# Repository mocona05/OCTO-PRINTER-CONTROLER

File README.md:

# OCTO-PRINTER TFT-LCD HAT MOUDLE (3D PRINTER)

**1. DC 7~30V INPUT(DC12V or DC24V, 5V 4A OUT)**

**2. POWER SUPPLY UNIT CONTROL( EXTERNAL RELAY CONTROL 12V or 24V Relay)**

**3. RGBW LED STRIP CONTROL(RED, BLUE, GREEN, WHITE LED FET SWITCHING CONTROL)**

https://ko.aliexpress.com/item/33022691125.html?spm=a2g0o.productlist.0.0.248165f1OyU0S3&algo_pvid=781429ec-3f9b-4be9-987b-c59219aeeffd&algo_expid=781429ec-3f9b-4be9-987b-c59219aeeffd-22&btsid=0bb0624416065510941383430e2371&ws_ab_test=searchweb0_0,searchweb201602_,searchweb201603_

**4. Raspberry SPI INTERFACE TFT-LCD & TOUCH SUPPORT**

https://ko.aliexpress.com/item/32233522592.html?spm=a2g0s.9042311.0.0.5f7c4c4dNYOjiv

**5. ENCLOSURE-CONTROL SUPPORT (HUMIDITY, TEMPERATURE MONITORING, OUTPUT RELAY 4CHANNEL CONTROL SUPPORT)**

**6. Raspberry Pi AP Cooling FAN(5V, PWM Speed Control)**

**7. Klipper ADXL345 Sensor Connector Bulit in(ADXL345 resonance sensor cannot be used simultaneously with SPI-LCD.)**

https://www.klipper3d.org/Measuring_Resonances.html

For more information, see WIKI.<br>
https://github.com/mocona05/OCTO-PRINTER-CONTROLER/wiki

Application of Octo Printer Shiled<br>
https://www.thingiverse.com/make:639404

LCD module Pi TFT 3.5 inch (320*480) Touchscreen Display Module

**TOUCH GHI SETTING**

OCTO PRINTER IMAGE DOWN LOAD
https://octoprint.org/download/

OCTO PRINTER IMAGE to SD MEMORY WRITE

https://www.raspberrypi.org/forums/viewtopic.php?t=131489
https://www.raspberrypi.org/forums/viewtopic.php?p=890408#p890408

**RASPBERRY PI FIRMWARE UPDATE**

`sudo rpi-update`

**RASPBERRY PI UPDATE**

`sudo apt-get update`<br>
`sudo apt-get upgrade`<br>

**RASPBERRY PI XWINDOWS INSTALL**

`sudo apt-get install --no-install-recommends xserver-xorg`<br>
`sudo apt-get install --no-install-recommends xinit`<br>
`sudo apt-get install raspberrypi-ui-mods`<br>

**xwindos auto login & Pi camera setting**

`sudo raspi-config`<br>
3.Boot-option -> B1 Desktop /CLI -> B4 Desktop Autologin

Pi CAMERA SETUP (Raspberry pi camera used)
5. Interfacing Optin -> Pi Camera -> Yes

7.Advanced Options -> A1 Expand Filesystem

**TFT DRIVER INSTALL**

https://www.waveshare.com/wiki/3.5inch_RPi_LCD_(A)#Method_1._Driver_installation

`wget https://www.waveshare.com/w/upload/1/1e/LCD-show-180817.tar.gz`<br>

**DRIVER extractor**

`tar xvf LCD-show-180817.tar.gz`<br>
`cd LCD-show/`<br>
`chmod 777 LCD35-show`<br>
`./LCD35-show`<br>

**HDMI & TOUCH DRIVER INSTALL**

https://www.raspberrypi.org/forums/viewtopic.php?t=175616

`sudo apt-get install xinput-calibrator`<br>

**CHROMIUM INSTALL**

`sudo apt-get install unclutter`<br>
`sudo apt-get install xdotool`<br>

https://raspberrypi.stackexchange.com/questions/374/how-do-i-install-google-chrome

`sudo apt-get install chromium-browser`<br>

**CHROMIUM AUTO START SETTING**

https://www.raspberrypi.org/forums/viewtopic.php?t=163316

`sudo nano ~/.config/lxsession/LXDE-pi/autostart`<br>
`sudo -u pi chromium-browser --kiosk --incognito http://127.0.0.1 &`<br>

`sudo reboot`

connect at http://<your Raspberry pi's IP>

**PSU Control Plug In Setup**

**LED Strip Control Plug in Setup**

**TouchUI Plug in Setup**

**USB CAM Install(Option)**

https://github.com/jacksonliam/mjpg-streamer/

`sudo apt-get install subversion libjpeg8-dev libav-tools libv4l-dev cmake`<br>
`git clone https://github.com/jacksonliam/mjpg-streamer.git`<br>
`cd mjpg-streamer/mjpg-streamer-experimental`<br>
`export LD_LIBRARY_PATH=.`<br>
`sudo make`<br>

Connecting camera repeat command.

`ls /dev/video*`<br> 
(If you see the / dev / video0, then everything should be fine, go ahead)

ttps://github.com/foosel/OctoPrint/wiki/MJPG-Streamer-configuration

`sudo ./mjpg_streamer –i "./input_uvc.so –f 2 -y" -o "./output_http.so"`

check at http://<your Raspberry pi's IP>:8080/?action=stream

`sudo usermod -a -G video pi`<br>
(to allow user access to a device video, it is necessary to add it to the appropriate group)

`sudo make install`<br>
`cd ~`<br>
`sudo nano webcam-streamer`<br>

`#!/bin/bash`<br>
`Daemon=mjpg_streamer`<br>
`DaemonBase=/usr/local`<br>
`DaemonArgs="-i \"input_uvc.so –f 2 -y\" -o \"output_http.so\""`<br>
`case "" in`<br>
`start)`<br>
`eval LD_LIBRARY_PATH=${DaemonBase}/lib ${DaemonBase}/bin/${Daemon} ${DaemonArgs} >/dev/null 2>&1 &`<br>
`echo ": started"`<br>
`;;`<br>
`stop)`<br>
`pkill -x ${Daemon}`<br>
`echo ": stopped"`<br>
`;;`<br>
`*)`<br>
`echo "Usage:  {start|stop}" >&2`<br>
`;;`<br>
`Esac`<br>

`sudo chmod +x webcam-streamer`<br>
`sudo mv webcam-streamer /usr/local/bin/`<br>
`sudo nano ~/.octoprint/config.yaml`<br>

`system:`<br>
  `actions:`<br>
  `- action: streamon`<br>
    `command: sudo /usr/local/bin/webcam-streamer start`<br>
    `confirm: false`<br>
    `name: Start video stream`<br>
  `- action: streamoff`<br>
    `command: sudo /usr/local/bin/webcam-streamer stop`<br>
    `confirm: false`<br>
    `name: Stop video stream`<br>

**Auto start cam**

`sudo nano /etc/rc.local`<br>

`usr/local/bin/webcam-streamer start`<br>
(Just make sure to put it above the line that reads exit 0).

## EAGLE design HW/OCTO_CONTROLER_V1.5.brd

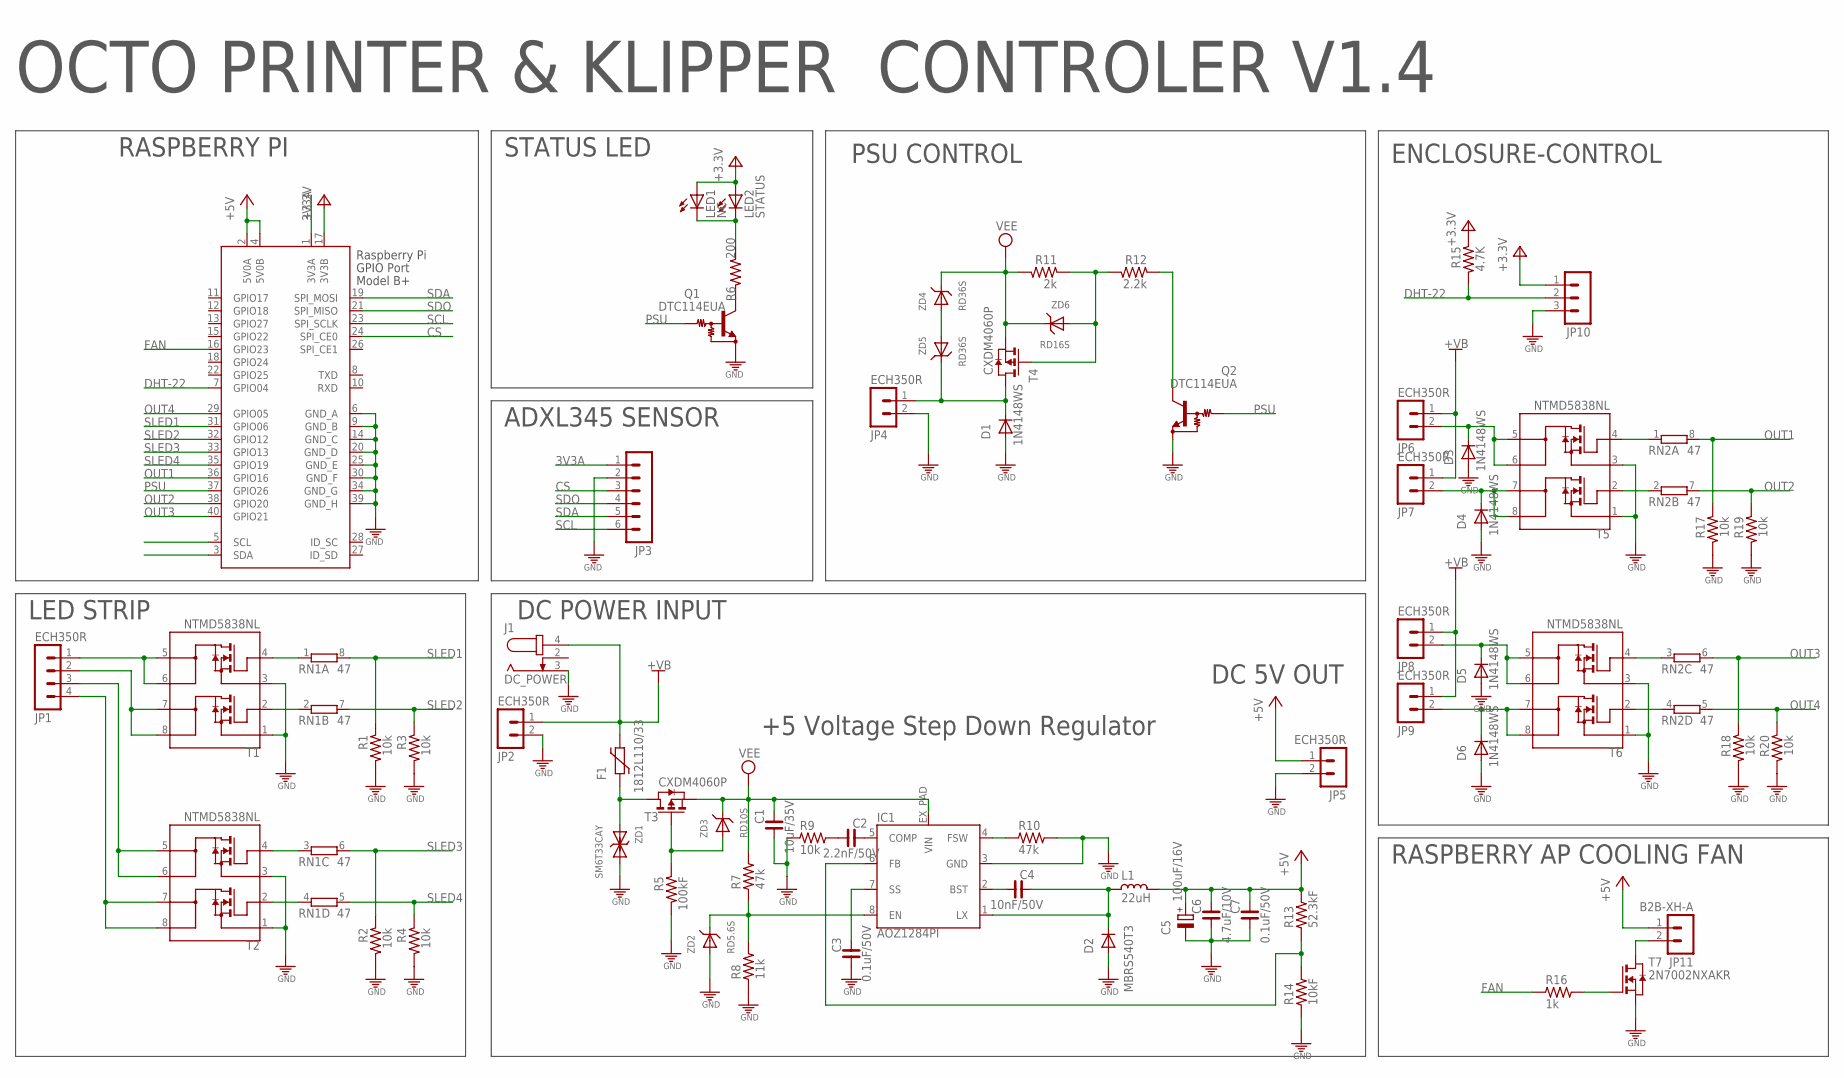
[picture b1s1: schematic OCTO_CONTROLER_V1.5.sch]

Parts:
C1: 10uF/35V; C3225
C2: 2.2nF/50V; C0603
C3, C7: 0.1uF/50V; C0603
C4: 10nF/50V; C0603
C5: 100uF/16V; D/7343-31W
C6: 4.7uF/10V; C2012
D1, D3, D4, D5, D6: 1N4148WS; SOD323
D2: MBRS540T3; SMC
F1: 1812L110/33; 1812L
IC1: AOZ1284PI; S08-EP1
J1: DC_POWER; DC-005
JP1: ECH350R; ECH350R-04
JP2, JP4, JP6, JP7, JP8, JP9: ECH350R; ECH350R-02
JP3: MA06-1SMALL; MA06-1-S
JP5: ECH350R; ECH350V-02
JP10: MA03-1ECH350R; ECH350R-03
JP11: B2B-XH-A; MOLEX5267-02
L1: 22uH; SHP1260P-F
LED1: NC; LED-1608
LED2: STATUS; 3FG2HD-T1
Q1, Q2: DTC114EUA; SC59-BEC
R1, R2, R3, R4, R9, R17, R18, R19, R20: 10k; R0603
R5: 100kF; R0603
R6: 200; R0603
R7, R10: 47k; R0603
R8: 11k; R0603
R11: 2k; R0603
R12: 2.2k; R0603
R13: 52.3kF; R0603
R14: 10kF; R0603
R15: 4.7K; R0603
R16: 1k; R0603
RN1, RN2: 47; ARRAY_R3216
T1, T2, T5, T6: NTMD5838NL; SO08
T3, T4: CXDM4060P; SOT89
T7: 2N7002NXAKR; SOT23
X1: RASPI_BOARD_B+#_F; RASPI_BOARD_B+_FULL
ZD1: SM6T33CAY; SMB
ZD2: RD5.6S; DSMM
ZD3: RD10S; DSMM
ZD4, ZD5: RD36S; DSMM
ZD6: RD16S; DSMM

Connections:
3V3: JP10.1, LED1.A, LED2.A, R15.1, X1.17 (3V3B)
3V3A: JP3.1, X1.1 (3V3A)
+5V: C5.+, C6.1, C7.1, JP5.1, JP11.1, L1.1, R13.2, X1.2 (5V0A), X1.4 (5V0B)
+12V: F1.P$2 (2), J1.4 (3), JP2.1, JP6.1, JP7.1, JP8.1, JP9.1
CS: JP3.3, X1.24 (SPI_CE0)
DC-IN: F1.P$1 (1), T3.2 (D), T3.2@1 (D), ZD1.A
DHT-22: JP10.2, R15.2, X1.7 (GPIO04)
FAN: R16.1, X1.16 (GPIO23)
GND: C1.2, C3.2, C5.-, C6.2, C7.2, D1.A, D2.A, D3.A, D4.A, D5.A, D6.A, IC1.3 (GND), J1.3 (1), JP2.2, JP3.2, JP4.2, JP5.2, JP10.3, Q1.1 (GND), Q2.1 (GND), R1.2, R2.2, R3.2, R4.2, R5.2, R8.1, R9.1, R10.2, R14.1, R17.2, R18.2, R19.2, R20.2, T1.1, T1.3, T2.1, T2.3, T5.1, T5.3, T6.1, T6.3, T7.S, X1.6 (GND_A), X1.9 (GND_B), X1.14 (GND_C), X1.20 (GND_D), X1.25 (GND_E), X1.30 (GND_F), X1.34 (GND_G), X1.39 (GND_H), ZD1.C (K), ZD2.A
unnamed: R11.1, R12.2, T4.3 (G), ZD6.A
unnamed: LED1.C, LED2.K (C), R6.1
unnamed: ZD4.A, ZD5.A
unnamed: RN1.2 (1), T1.2
unnamed: RN1.1, T1.4
unnamed: RN1.4 (1), T2.2
unnamed: JP11.2, T7.D
unnamed: R16.2, T7.G
unnamed: IC1.6 (FB), R13.1, R14.2
unnamed: RN1.3 (1), T2.4
unnamed: C4.2, IC1.2 (BST)
unnamed: D1.C, JP4.1, T4.2 (D), T4.2@1 (D), ZD5.C
unnamed: RN2.2 (1), T5.2
unnamed: RN2.1, T5.4
unnamed: D3.C, JP6.2, T5.5, T5.6
unnamed: D4.C, JP7.2, T5.7, T5.8
unnamed: RN2.4 (1), T6.2
unnamed: RN2.3 (1), T6.4
unnamed: C4.1, D2.C, IC1.1 (LX), L1.2
unnamed: IC1.4 (FSW), R10.1
unnamed: C3.1, IC1.7 (SS)
unnamed: IC1.8 (EN), R7.1, R8.2, ZD2.C
unnamed: C2.1, IC1.5 (COMP)
unnamed: Q2.3 (OUT), R12.1
unnamed: D5.C, JP8.2, T6.5, T6.6
unnamed: C2.2, R9.2
unnamed: D6.C, JP9.2, T6.7, T6.8
unnamed: Q1.3 (OUT), R6.2
unnamed: R5.1, T3.3 (G), ZD3.A
OUT1: R17.1, RN2.8 (2), X1.36 (GPIO16)
OUT2: R19.1, RN2.7 (2), X1.38 (GPIO20)
OUT3: R18.1, RN2.6 (2), X1.40 (GPIO21)
OUT4: R20.1, RN2.5 (2), X1.29 (GPIO05)
PSU: Q1.2 (IN), Q2.2 (IN), X1.37 (GPIO26)
S-LED1: JP1.1, T1.5, T1.6
S-LED2: JP1.2, T1.7, T1.8
S-LED3: JP1.3, T2.5, T2.6
S-LED4: JP1.4, T2.7, T2.8
SCL: JP3.6, X1.23 (SPI_SCLK)
SDA: JP3.5, X1.19 (SPI_MOSI)
SDO: JP3.4, X1.21 (SPI_MISO)
SLED1: R1.1, RN1.8 (2), X1.31 (GPIO06)
SLED2: R3.1, RN1.7 (2), X1.32 (GPIO12)
SLED3: R2.1, RN1.6 (2), X1.33 (GPIO13)
SLED4: R4.1, RN1.5 (2), X1.35 (GPIO19)
VEE: C1.1, IC1.EX_PAD (VIN), R7.2, R11.2, T3.1 (S), T4.1 (S), ZD3.C, ZD4.C, ZD6.C

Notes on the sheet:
OCTO PRINTER & KLIPPER CONTROLER V1.4
RASPBERRY PI
+5 Voltage Step Down Regulator
DC POWER INPUT
PSU CONTROL
STATUS LED
LED STRIP
DC 5V OUT
ENCLOSURE-CONTROL
ADXL345 SENSOR
RASPBERRY AP COOLING FAN

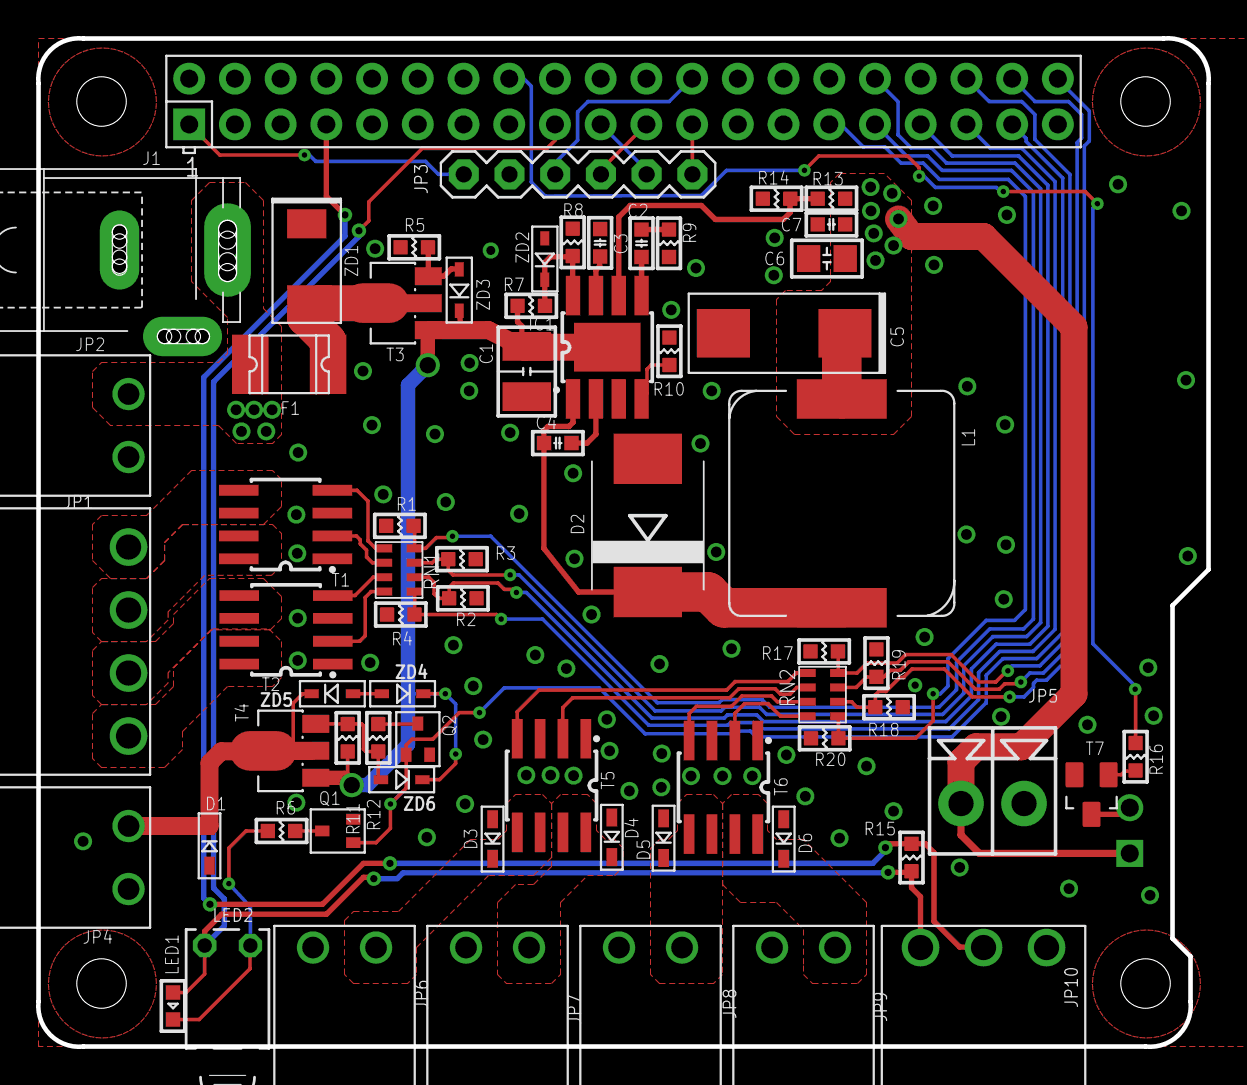
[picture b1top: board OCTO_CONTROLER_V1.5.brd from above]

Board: 2 copper layers, 65.0 x 56.0 mm, 68 parts (1 on the bottom side), 55 nets.

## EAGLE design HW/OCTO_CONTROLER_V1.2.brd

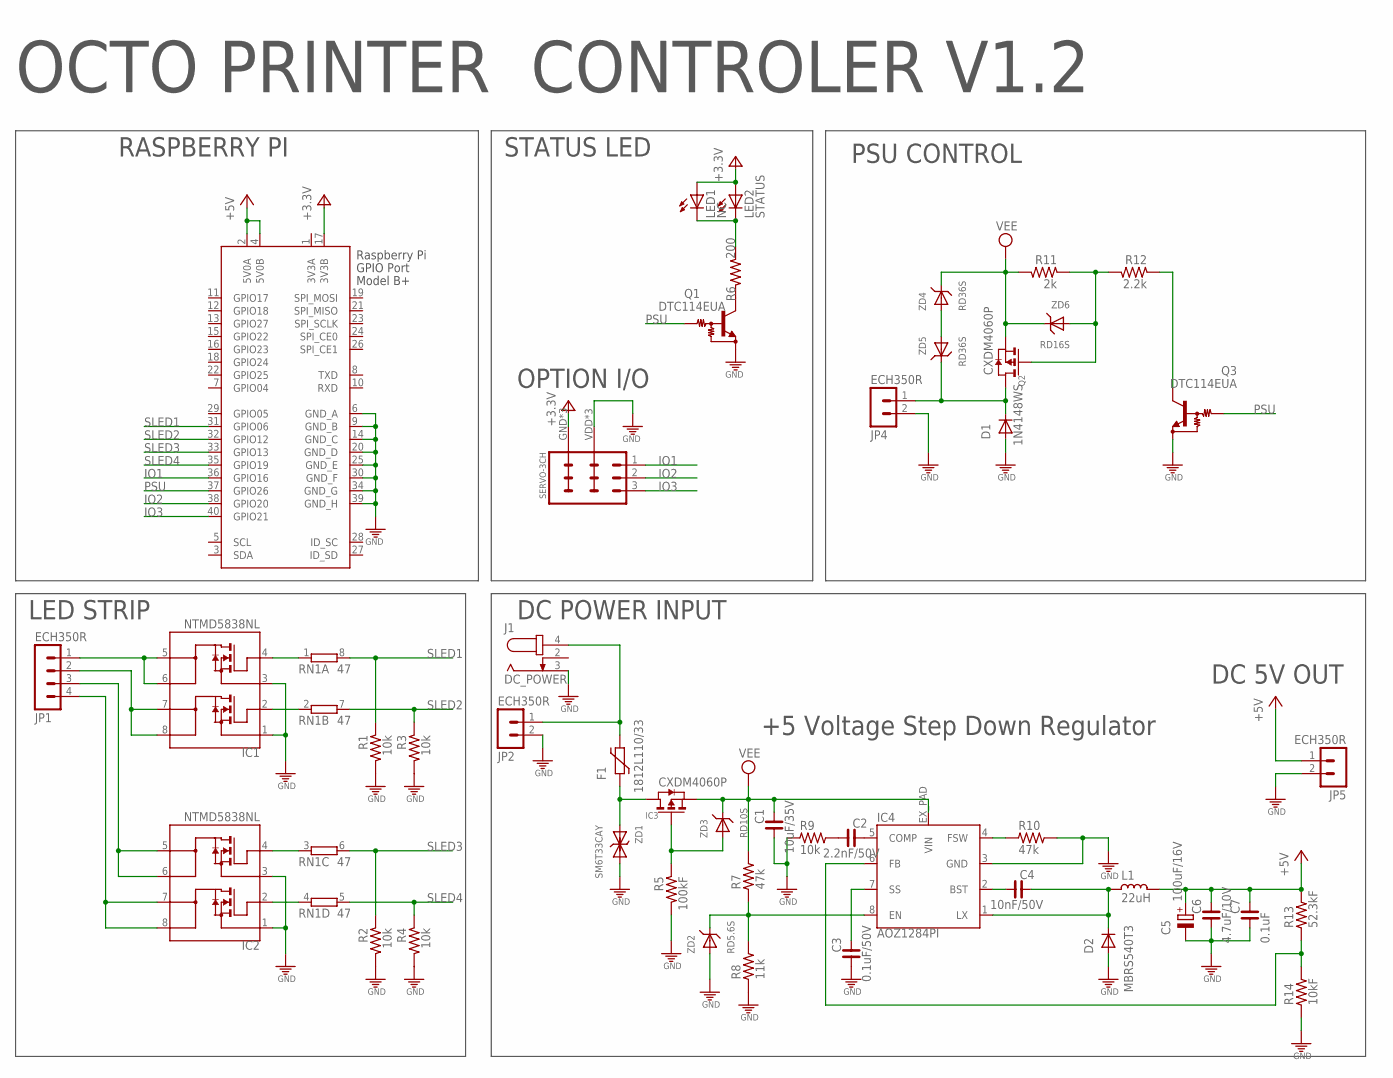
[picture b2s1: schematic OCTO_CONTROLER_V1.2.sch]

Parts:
C1: 10uF/35V; C3225
C2: 2.2nF/50V; C0603
C3: 0.1uF/50V; C0603
C4: 10nF/50V; C0603
C5: 100uF/16V; D/7343-31W
C6: 4.7uF/10V; C2012
C7: 0.1uF; C0603
D1: 1N4148WS; SOD323
D2: MBRS540T3; SMC
F1: 1812L110/33; 1812L
IC1, IC2: NTMD5838NL; SO08
IC3: CXDM4060P; SOT89
IC4: AOZ1284PI; S08-EP1
J1: DC_POWER; DC-005
JP1: ECH350R; ECH350R-04
JP2, JP4, JP5: ECH350R; ECH350R-02
JP3: SERVO-3CH; SERVO-3CH1
L1: 22uH; SHP1260P-F
LED1: NC; LED-1608
LED2: STATUS; 3FG2HD-T1
Q1, Q3: DTC114EUA; SC59-BEC
Q2: CXDM4060P; SOT89
R1, R2, R3, R4, R9: 10k; R0603
R5: 100kF; R0603
R6: 200; R0603
R7, R10: 47k; R0603
R8: 11k; R0603
R11: 2k; R0603
R12: 2.2k; R0603
R13: 52.3kF; R0603
R14: 10kF; R0603
RN1: 47; ARRAY_R3216
X1: RASPI_BOARD_B+#_F; RASPI_BOARD_B+_FULL
ZD1: SM6T33CAY; SMB
ZD2: RD5.6S; DSMM
ZD3: RD10S; DSMM
ZD4, ZD5: RD36S; DSMM
ZD6: RD16S; DSMM

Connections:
3V3: JP3.GND, JP3.GND@1 (GND), JP3.GND@2 (GND), LED1.A, LED2.A, X1.17 (3V3B)
3V3A: X1.1 (3V3A)
+5V: C5.+, C6.1, C7.1, JP5.1, L1.1, R13.2, X1.2 (5V0A), X1.4 (5V0B)
DC-IN: F1.P$1 (1), IC3.2 (D), IC3.2@1 (D), ZD1.A
GND: C1.2, C3.2, C5.-, C6.2, C7.2, D1.A, D2.A, IC1.1, IC1.3, IC2.1, IC2.3, IC4.3 (GND), J1.3 (1), JP2.2, JP3.VDD (+5V), JP3.VDD@1 (+5V), JP3.VDD@2 (+5V), JP4.2, JP5.2, Q1.1 (GND), Q3.1 (GND), R1.2, R2.2, R3.2, R4.2, R5.2, R8.1, R9.1, R10.2, R14.1, X1.6 (GND_A), X1.9 (GND_B), X1.14 (GND_C), X1.20 (GND_D), X1.25 (GND_E), X1.30 (GND_F), X1.34 (GND_G), X1.39 (GND_H), ZD1.C (K), ZD2.A
IO1: JP3.1, X1.36 (GPIO16)
IO2: JP3.2, X1.38 (GPIO20)
IO3: JP3.3, X1.40 (GPIO21)
unnamed: Q2.3 (G), R11.1, R12.2, ZD6.A
unnamed: LED1.C, LED2.K (C), R6.1
unnamed: ZD4.A, ZD5.A
unnamed: IC1.2, RN1.2 (1)
unnamed: IC1.4, RN1.1
unnamed: IC2.2, RN1.4 (1)
unnamed: IC4.6 (FB), R13.1, R14.2
unnamed: IC2.4, RN1.3 (1)
unnamed: C4.2, IC4.2 (BST)
unnamed: D1.C, JP4.1, Q2.2 (D), Q2.2@1 (D), ZD5.C
unnamed: C4.1, D2.C, IC4.1 (LX), L1.2
unnamed: IC4.4 (FSW), R10.1
unnamed: C3.1, IC4.7 (SS)
unnamed: IC4.8 (EN), R7.1, R8.2, ZD2.C
unnamed: C2.1, IC4.5 (COMP)
unnamed: Q3.3 (OUT), R12.1
unnamed: C2.2, R9.2
unnamed: Q1.3 (OUT), R6.2
unnamed: IC3.3 (G), R5.1, ZD3.A
unnamed: F1.P$2 (2), J1.4 (3), JP2.1
PSU: Q1.2 (IN), Q3.2 (IN), X1.37 (GPIO26)
S-LED1: IC1.5, IC1.6, JP1.1
S-LED2: IC1.7, IC1.8, JP1.2
S-LED3: IC2.5, IC2.6, JP1.3
S-LED4: IC2.7, IC2.8, JP1.4
SLED1: R1.1, RN1.8 (2), X1.31 (GPIO06)
SLED2: R3.1, RN1.7 (2), X1.32 (GPIO12)
SLED3: R2.1, RN1.6 (2), X1.33 (GPIO13)
SLED4: R4.1, RN1.5 (2), X1.35 (GPIO19)
VEE: C1.1, IC3.1 (S), IC4.EX_PAD (VIN), Q2.1 (S), R7.2, R11.2, ZD3.C, ZD4.C, ZD6.C

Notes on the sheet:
OCTO PRINTER CONTROLER V1.2
RASPBERRY PI
+5 Voltage Step Down Regulator
DC POWER INPUT
PSU CONTROL
STATUS LED
OPTION I/O
LED STRIP
DC 5V OUT

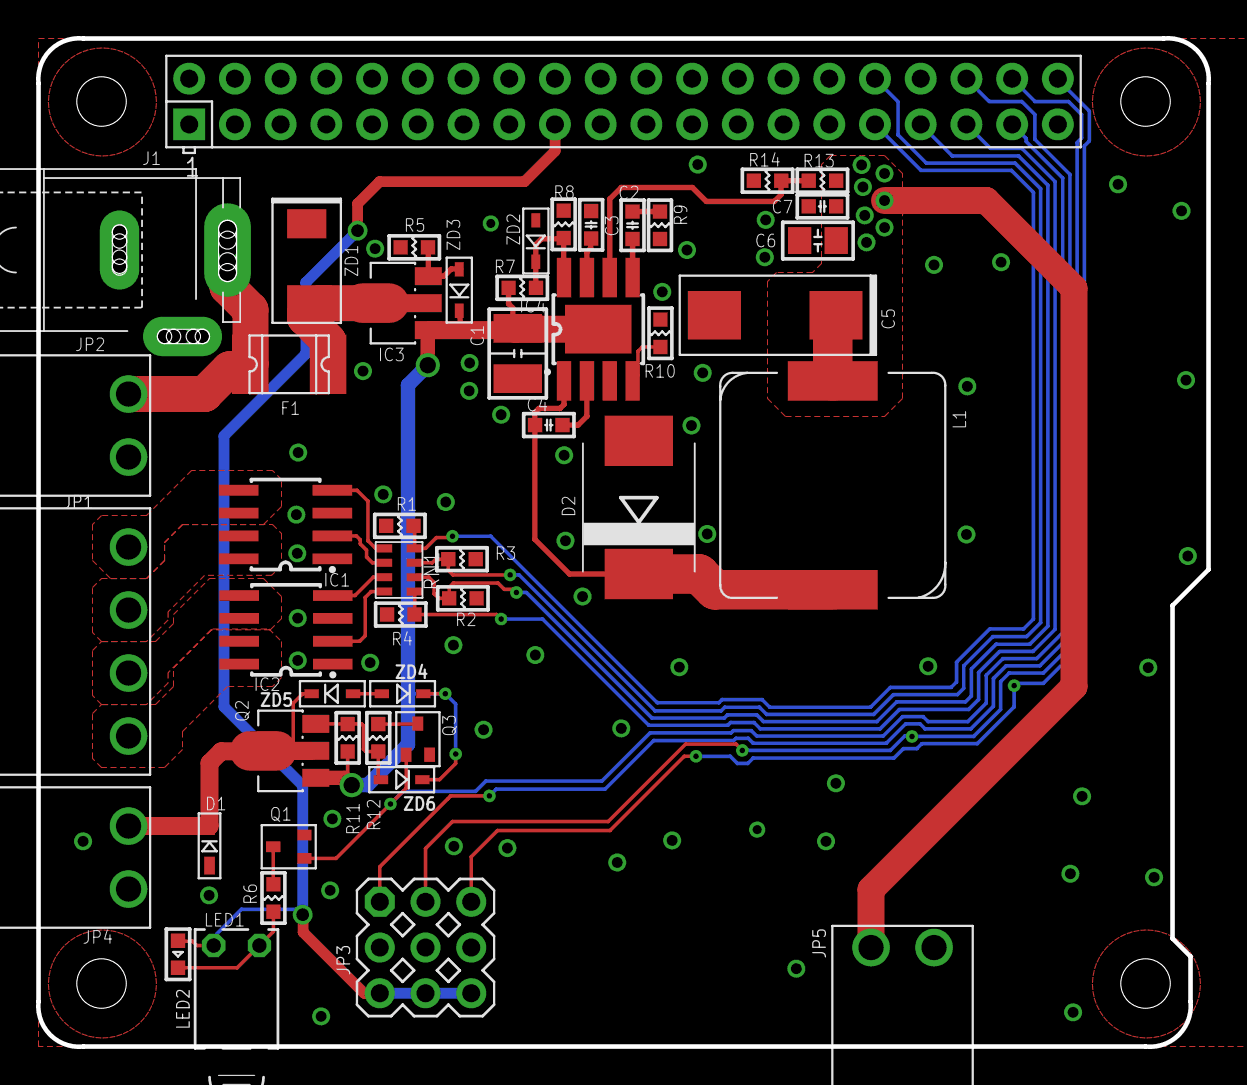
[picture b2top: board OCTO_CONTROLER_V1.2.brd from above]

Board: 2 copper layers, 65.0 x 56.0 mm, 48 parts (0 on the bottom side), 37 nets.

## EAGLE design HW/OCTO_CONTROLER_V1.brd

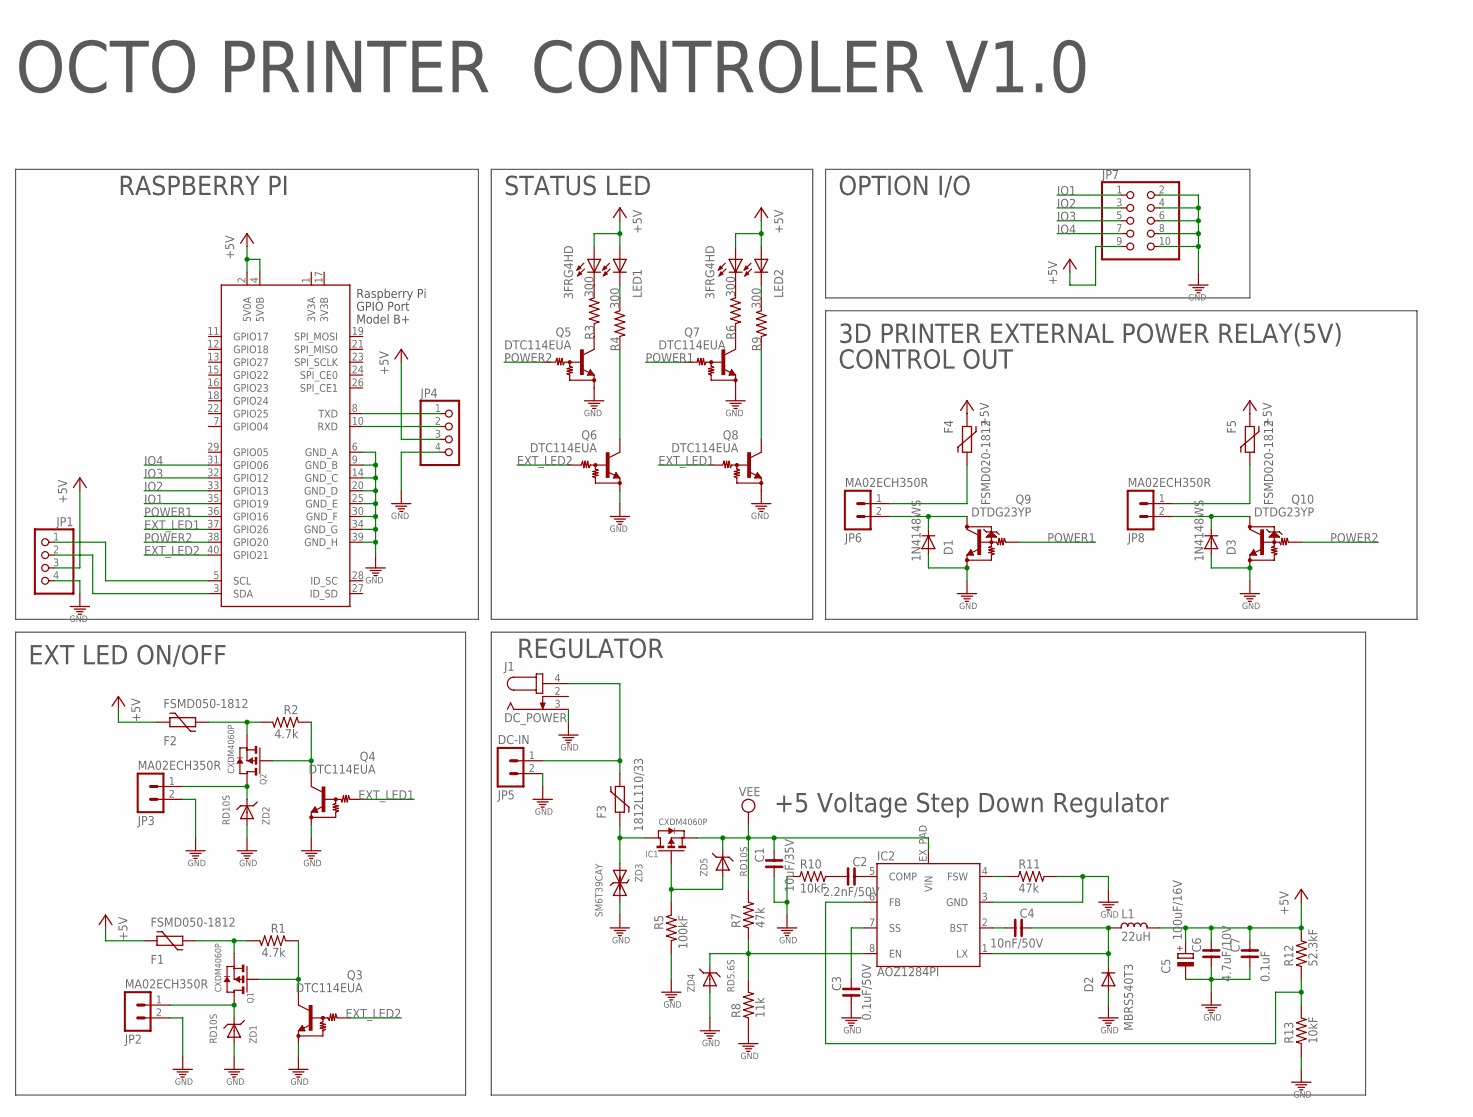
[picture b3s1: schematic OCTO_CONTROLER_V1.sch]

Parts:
C1: 10uF/35V; C3225
C2: 2.2nF/50V; C0603
C3: 0.1uF/50V; C0603
C4: 10nF/50V; C0603
C5: 100uF/16V; D/7343-31W
C6: 4.7uF/10V; C2012
C7: 0.1uF; C0603
D1, D3: 1N4148WS; SOD323
D2: MBRS540T3; SMC
F1, F2: FSMD050-1812; 1812L
F3: 1812L110/33; 1812L
F4, F5: FSMD020-1812; 1812L
IC1: CXDM4060P; SOT89
IC2: AOZ1284PI; S08-EP1
J1: DC_POWER; DC-005
JP1, JP4: PINHD-1X4; 1X04
JP2, JP3, JP6, JP8: MA02ECH350R; ECH350R-02
JP5: DC-IN; ECH350R-02
JP7: PINHD-2X5/90; 2X05/90
L1: 22uH; SHP1260P-F
LED1, LED2: 3FRG4HD; 3FRG4H
Q1, Q2: CXDM4060P; SOT89
Q3, Q4, Q5, Q6, Q7, Q8: DTC114EUA; SC59-BEC
Q9, Q10: DTDG23YP; MPT3
R1, R2: 4.7k; R0603
R3, R4, R6, R9: 300; R0603
R5: 100kF; R0603
R7, R11: 47k; R0603
R8: 11k; R0603
R10, R13: 10kF; R0603
R12: 52.3kF; R0603
X1: RASPI_BOARD_B+#_F; RASPI_BOARD_B+_FULL
ZD1, ZD2, ZD5: RD10S; DSMM
ZD3: SM6T39CAY; SMB
ZD4: RD5.6S; DSMM

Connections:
3V3A: X1.1 (3V3A)
3V3B: X1.17 (3V3B)
+5V: C5.+, C6.1, C7.1, F1.P$1 (1), F2.P$1 (1), F4.P$1 (1), F5.P$1 (1), JP1.3, JP4.3, JP7.9, L1.1, LED1.A (A1), LED1.A1 (A2), LED2.A (A1), LED2.A1 (A2), R12.2, X1.2 (5V0A), X1.4 (5V0B)
DC-IN: F3.P$1 (1), IC1.2 (D), IC1.2@1 (D), ZD3.A
EXT_LED1: Q4.2 (IN), Q8.2 (IN), X1.37 (GPIO26)
EXT_LED2: Q3.2 (IN), Q6.2 (IN), X1.40 (GPIO21)
GND: C1.2, C3.2, C5.-, C6.2, C7.2, D1.A, D2.A, D3.A, IC2.3 (GND), J1.3 (1), JP1.4, JP2.2, JP3.2, JP4.4, JP5.2, JP7.2, JP7.4, JP7.6, JP7.8, JP7.10, Q3.1 (GND), Q4.1 (GND), Q5.1 (GND), Q6.1 (GND), Q7.1 (GND), Q8.1 (GND), Q9.EMITTER (GND), Q10.EMITTER (GND), R5.2, R8.1, R10.1, R11.2, R13.1, X1.6 (GND_A), X1.9 (GND_B), X1.14 (GND_C), X1.20 (GND_D), X1.25 (GND_E), X1.30 (GND_F), X1.34 (GND_G), X1.39 (GND_H), ZD1.A, ZD2.A, ZD3.C (K), ZD4.A
IO1: JP7.1, X1.35 (GPIO19)
IO2: JP7.3, X1.33 (GPIO13)
IO3: JP7.5, X1.32 (GPIO12)
IO4: JP7.7, X1.31 (GPIO06)
unnamed: D1.C, JP6.2, Q9.COLLECTOR (OUT)
unnamed: Q1.3 (G), Q3.3 (OUT), R1.1
unnamed: JP2.1, Q1.2 (D), Q1.2@1 (D), ZD1.C
unnamed: F2.P$2 (2), Q2.1 (S), R2.2
unnamed: F1.P$2 (2), Q1.1 (S), R1.2
unnamed: D3.C, JP8.2, Q10.COLLECTOR (OUT)
unnamed: F5.P$2 (2), JP8.1
unnamed: F4.P$2 (2), JP6.1
unnamed: IC2.6 (FB), R12.1, R13.2
unnamed: JP1.1, X1.5 (SCL)
unnamed: C4.2, IC2.2 (BST)
unnamed: JP3.1, Q2.2 (D), Q2.2@1 (D), ZD2.C
unnamed: JP1.2, X1.3 (SDA)
unnamed: JP4.1, X1.8 (TXD)
unnamed: JP4.2, X1.10 (RXD)
unnamed: C4.1, D2.C, IC2.1 (LX), L1.2
unnamed: IC2.4 (FSW), R11.1
unnamed: C3.1, IC2.7 (SS)
unnamed: IC2.8 (EN), R7.1, R8.2, ZD4.C
unnamed: C2.1, IC2.5 (COMP)
unnamed: Q2.3 (G), Q4.3 (OUT), R2.1
unnamed: C2.2, R10.2
unnamed: Q5.3 (OUT), R3.2
unnamed: LED1.K (C1), R3.1
unnamed: LED1.K1 (C2), R4.1
unnamed: Q7.3 (OUT), R6.2
unnamed: LED2.K (C1), R6.1
unnamed: LED2.K1 (C2), R9.1
unnamed: Q8.3 (OUT), R9.2
unnamed: Q6.3 (OUT), R4.2
unnamed: IC1.3 (G), R5.1, ZD5.A
unnamed: F3.P$2 (2), J1.4 (3), JP5.1
POWER1: Q7.2 (IN), Q9.BASE (IN), X1.36 (GPIO16)
POWER2: Q5.2 (IN), Q10.BASE (IN), X1.38 (GPIO20)
VEE: C1.1, IC1.1 (S), IC2.EX_PAD (VIN), R7.2, ZD5.C

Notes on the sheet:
OCTO PRINTER CONTROLER V1.0
EXT LED ON/OFF
RASPBERRY PI
+5 Voltage Step Down Regulator
REGULATOR
3D PRINTER EXTERNAL POWER RELAY(5V)
STATUS LED
OPTION I/O
CONTROL OUT

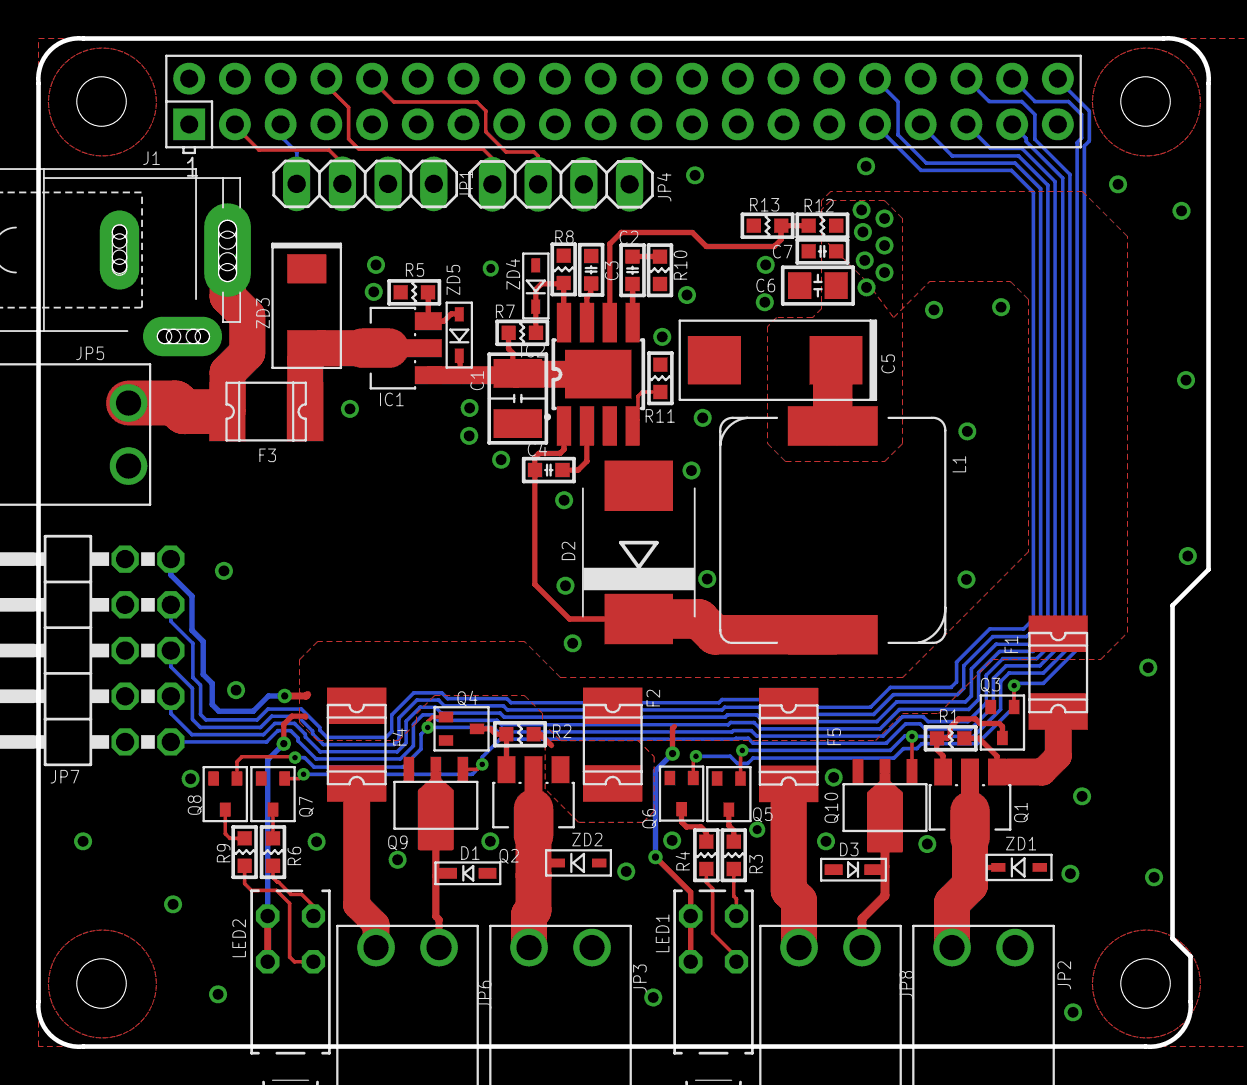
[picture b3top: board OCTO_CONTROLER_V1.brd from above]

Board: 2 copper layers, 65.0 x 56.0 mm, 58 parts (0 on the bottom side), 44 nets.

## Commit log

2018-07-23 PCB DESIGNE UPDATE
2018-07-23 RENAME PCB DESIGN FILE
2018-08-03 LED 저항값 수정
2018-09-04 OCTO PRINTER V1.2 PCB DESIGN
2018-09-04 v1.1 pcb gerber
2018-09-10 거버업로드
2018-10-02 v1.1수정
2018-10-12 v1.1 pcb
    image up load
2018-10-13 BOM & V1.2 PCB UPDATE
2018-10-13 pcb v1.2 silk update
2018-10-13 pdf update
2018-10-18 memual update
2018-10-19 menual update
2018-10-19 파일 정리
2018-10-19 sd image torrent upload
2018-10-19 menual update2
2018-10-19 update install manula pdf version
2018-10-20 bom pdf version update
2018-10-20 WIWRING MENUAL UPDATE
2018-10-21 image update
2018-11-03 V1.3 PCB UPDATE
    ENCLOSURE-CONTROL PART ADD-ON
2018-11-03 V1.3 PCB PATHC
    DHT-22 PULL-UP 10k->4.7K
2018-11-05 V1.3 PCB SILK UPDATE
2018-12-05 V1.3 PCB IMAGE UPDATE
2020-11-28 octo printer controler v1.4 update
    klipper support(adxl345)
    Raspberry Pi AP Cooling Fan Support
2020-11-28 v1.4 circuit pdf file upload
2020-11-28 Organize files
2020-11-28 V1.4 BOM UPDATE
2021-07-17 notebook change
2021-10-12 정기업로드
    정기업로드
